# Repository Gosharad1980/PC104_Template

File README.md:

# PC104 template PCB

PC104 form factor compliant with the PC104_Spec_v2_6

## PC104 ISA 8bits

---
## PC104 ISA 16bits

---
## PC104 LibreCube

---
## PC104 "PCI CAN Express"
Custom connector designed from the PCI-Express(x1) pin-out

	Liaison :
	 - PRSNT1# et PRSNT2# par le GNDD (équivalent présence carte PCIx1)
	
	Remplacement :
	 - SMBus -> I2C
	 - JTAG -> SPI dont SC1# et SC2#
	 - WAKE# -> CS3#
	 - CLKREQ -> CLKO
	 - RefClk différentielle PCI -> OSC1 et OSC2 pour external clock MCU
	 - HSOp(0) soit TX0 PCI -> ModBus A+
	 - HSOn(0) soit TX0 PCI -> ModBus B-
	 - HSIp(0) soit RXO PCI -> CAN_0_H
	 - HSIn(0) soit RXO PCI -> CAN_0_L
	
	PS : 
	L'utilisation d'un RS485 4 fils est possibles en cablant :
	 - HSOp(0) soit TX0 PCI -> DI_A+ master / RO_A+ slave(s)
	 - HSOn(0) soit TX0 PCI -> DI_B- master / RO_B- slave(s)
	 - HSIp(0) soit RXO PCI -> RO_A+ master / DI_A+ slave(s)
	 - HSIn(0) soit RXO PCI -> RO_B- master / DI_B- slave(s)

	L'utilisation d'un RS485 2 fils est possibles en cablant :
	 - HSOp(0) soit TX0 PCI -> A+ master / A+ slave
	 - HSOn(0) soit TX0 PCI -> B- master / B- slave
	 - HSIp(0) soit RXO PCI -> NC. ou CAN_0_H
	 - HSIn(0) soit RXO PCI -> NC. ou CAN_0_L

---

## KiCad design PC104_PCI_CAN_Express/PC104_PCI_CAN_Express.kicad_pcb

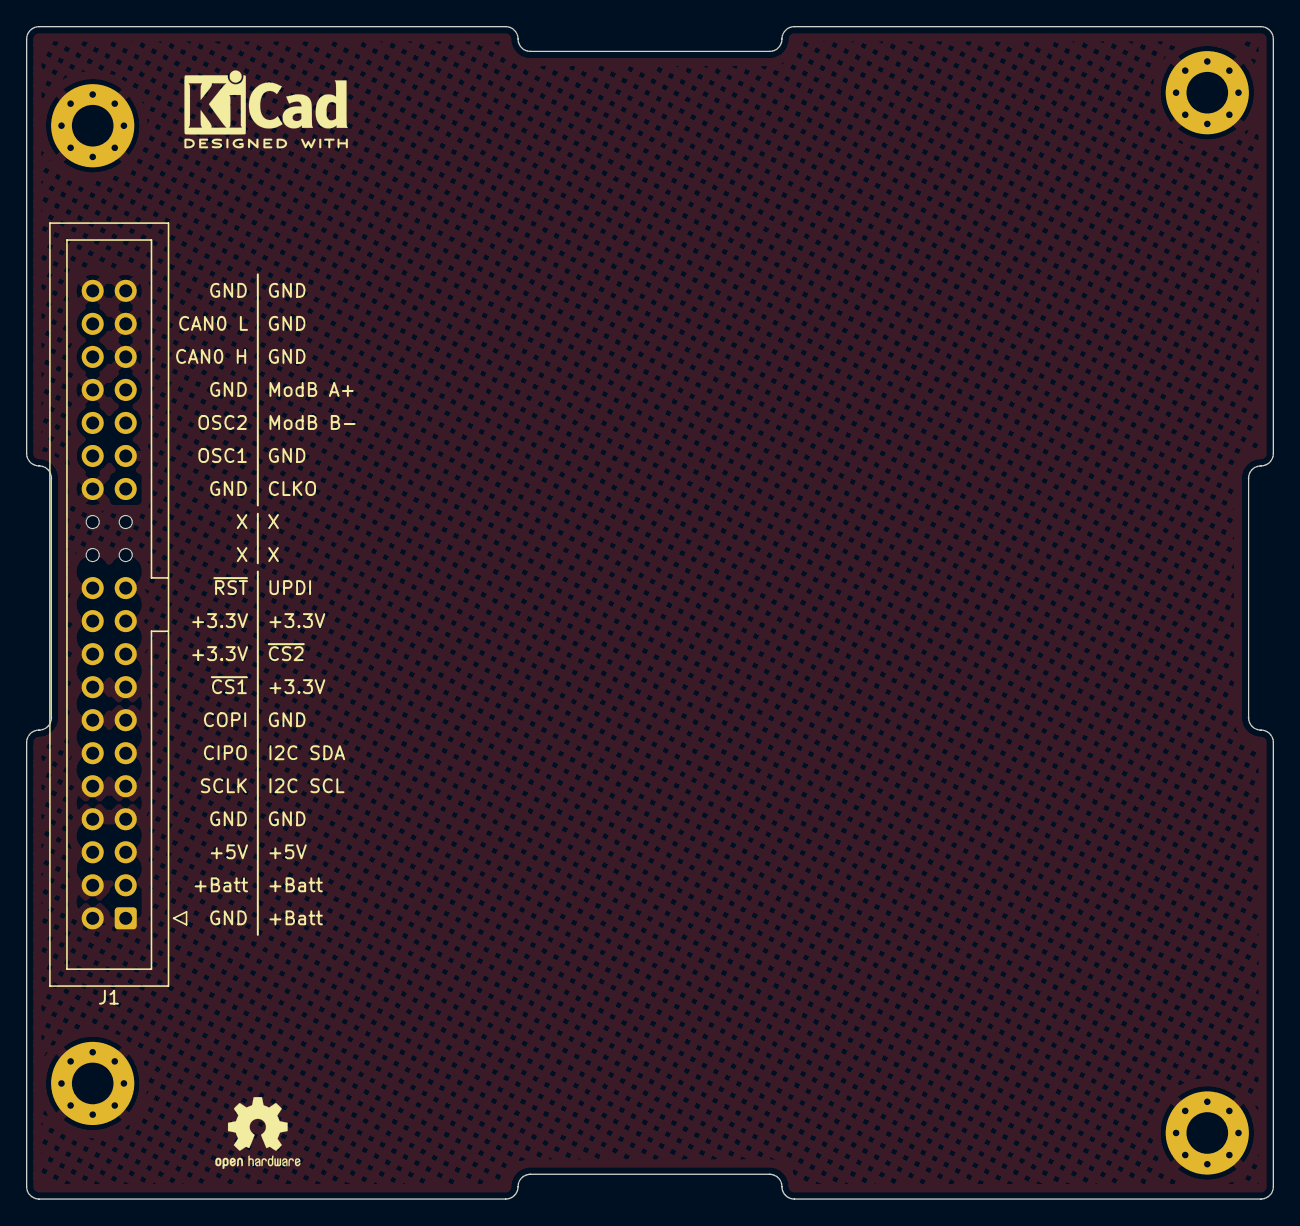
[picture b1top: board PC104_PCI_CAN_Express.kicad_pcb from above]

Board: 2 copper layers, 95.9 x 90.2 mm, 7 parts (0 on the bottom side), 4 nets, no tracks yet.

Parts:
H1, H2, H3, H4: MountingHole_Pad; MountingHole_3.2mm_M3_Pad_Via
J1: Conn_02x20_Odd_Even; IDC-Header_2x20_P2.54mm_Vertical
KiCad0: MountingHole; KiCad-Logo2_5mm_SilkScreen
OpenHW1: MountingHole; OSHW-Logo2_7.3x6mm_SilkScreen

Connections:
+3V3: J1.15, J1.18, J1.19, J1.20
+5V: J1.5, J1.6
+BATT: J1.1, J1.3, J1.4
GND: H1.1, H2.1, H3.1, H4.1, J1.2, J1.7, J1.8, J1.13, J1.28, J1.29, J1.34, J1.35, J1.37, J1.39, J1.40

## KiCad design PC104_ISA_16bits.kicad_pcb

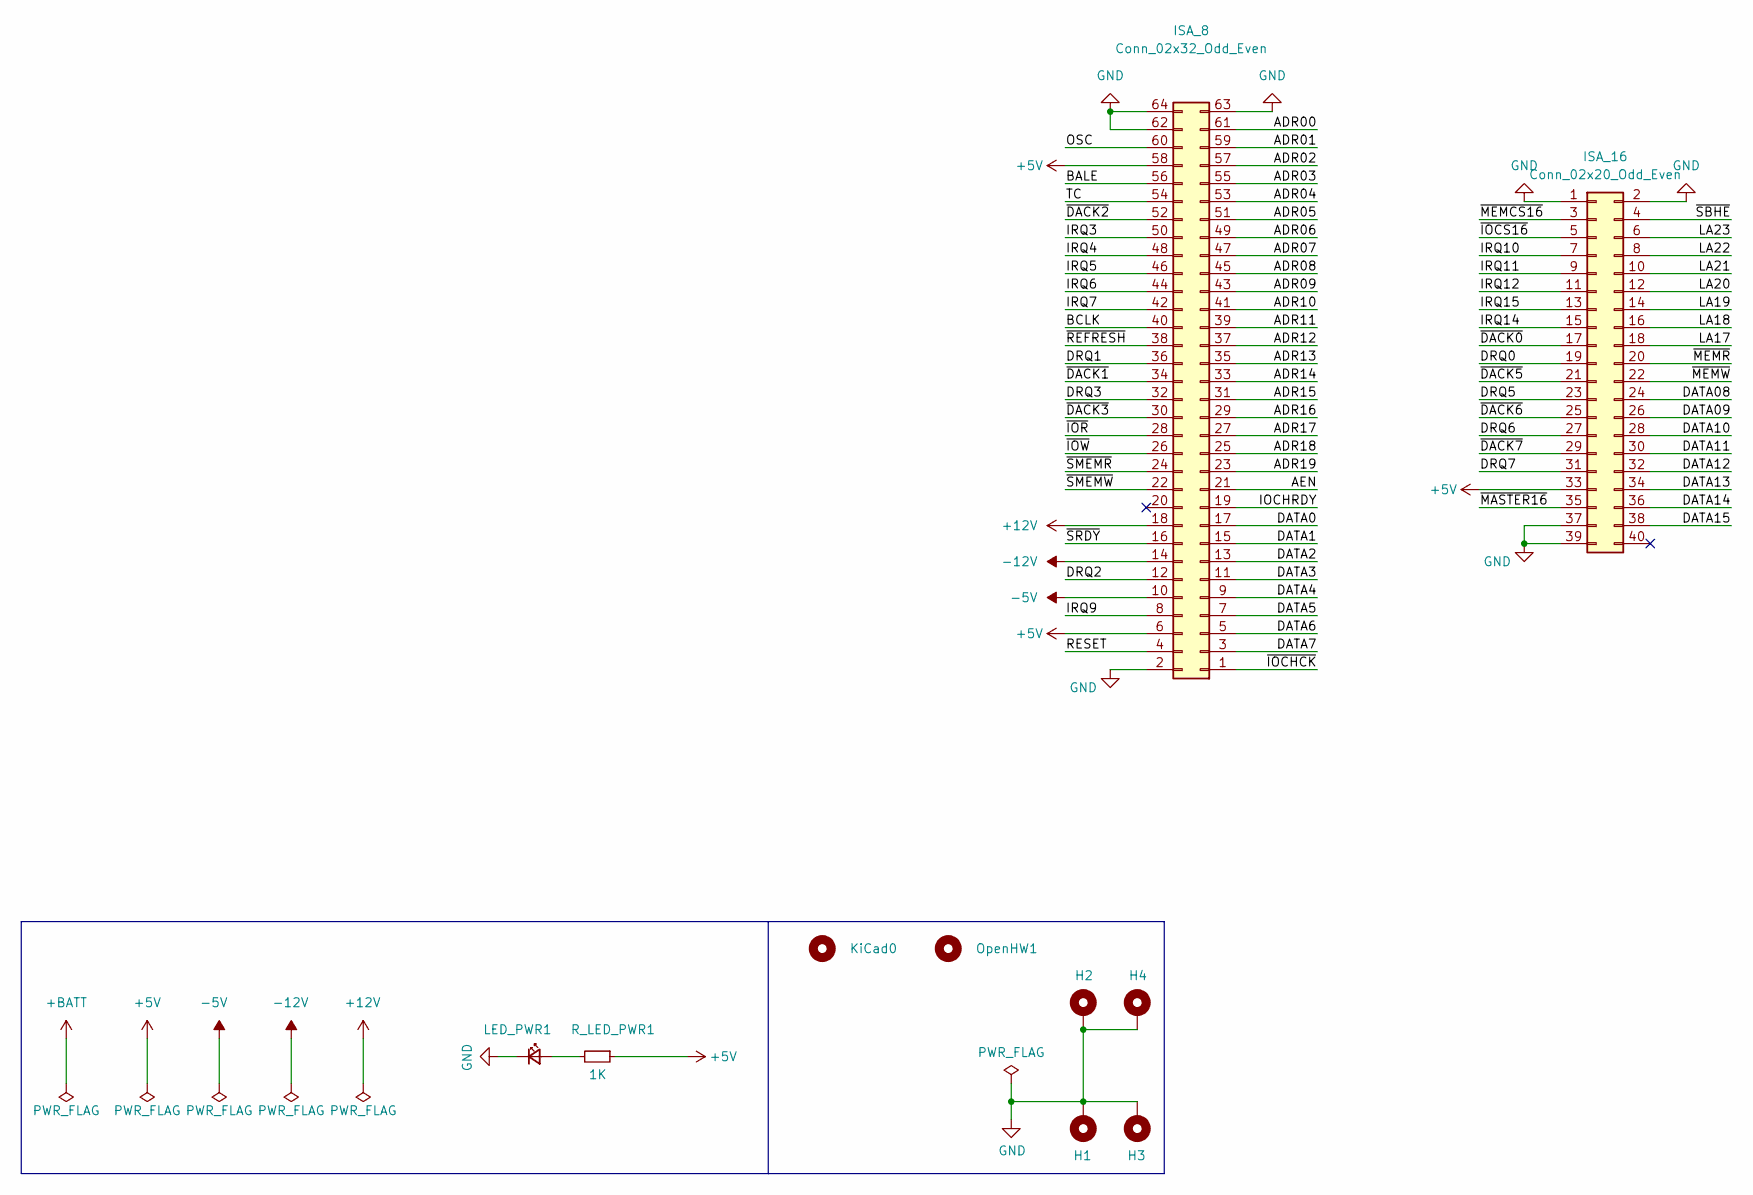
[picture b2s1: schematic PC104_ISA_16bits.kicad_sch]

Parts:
H1, H2, H3, H4: MountingHole_Pad; MountingHole_3.2mm_M3_DIN965_Pad
ISA_8: Conn_02x32_Odd_Even; PinHeader_2x32_P2.54mm_Vertical
ISA_16: Conn_02x20_Odd_Even; PinHeader_2x20_P2.54mm_Vertical
KiCad0: MountingHole; KiCad-Logo2_5mm_SilkScreen
LED_PWR1: LED; LED_1210_3225Metric_Pad1.42x2.65mm_HandSolder
OpenHW1: MountingHole; OSHW-Logo2_7.3x6mm_SilkScreen
R_LED_PWR1: 1K; R_1210_3225Metric_Pad1.30x2.65mm_HandSolder

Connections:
+5V: ISA_8.6, ISA_8.58, ISA_16.33, R_LED_PWR1.1
+12V: ISA_8.18
-5V: ISA_8.10
-12V: ISA_8.14
/ADR00: ISA_8.61
/ADR01: ISA_8.59
/ADR02: ISA_8.57
/ADR03: ISA_8.55
/ADR04: ISA_8.53
/ADR05: ISA_8.51
/ADR06: ISA_8.49
/ADR07: ISA_8.47
/ADR08: ISA_8.45
/ADR09: ISA_8.43
/ADR10: ISA_8.41
/ADR11: ISA_8.39
/ADR12: ISA_8.37
/ADR13: ISA_8.35
/ADR14: ISA_8.33
/ADR15: ISA_8.31
/ADR16: ISA_8.29
/ADR17: ISA_8.27
/ADR18: ISA_8.25
/ADR19: ISA_8.23
/AEN: ISA_8.21
/BALE: ISA_8.56
/BCLK: ISA_8.40
/DATA0: ISA_8.17
/DATA1: ISA_8.15
/DATA2: ISA_8.13
/DATA3: ISA_8.11
/DATA4: ISA_8.9
/DATA5: ISA_8.7
/DATA6: ISA_8.5
/DATA7: ISA_8.3
/DATA08: ISA_16.24
/DATA09: ISA_16.26
/DATA10: ISA_16.28
/DATA11: ISA_16.30
/DATA12: ISA_16.32
/DATA13: ISA_16.34
/DATA14: ISA_16.36
/DATA15: ISA_16.38
/DRQ0: ISA_16.19
/DRQ1: ISA_8.36
/DRQ2: ISA_8.12
/DRQ3: ISA_8.32
/DRQ5: ISA_16.23
/DRQ6: ISA_16.27
/DRQ7: ISA_16.31
/IOCHRDY: ISA_8.19
/IRQ3: ISA_8.50
/IRQ4: ISA_8.48
/IRQ5: ISA_8.46
/IRQ6: ISA_8.44
/IRQ7: ISA_8.42
/IRQ9: ISA_8.8
/IRQ10: ISA_16.7
/IRQ11: ISA_16.9
/IRQ12: ISA_16.11
/IRQ14: ISA_16.15
/IRQ15: ISA_16.13
/LA17: ISA_16.18
/LA18: ISA_16.16
/LA19: ISA_16.14
/LA20: ISA_16.12
/LA21: ISA_16.10
/LA22: ISA_16.8
/LA23: ISA_16.6
/OSC: ISA_8.60
/RESET: ISA_8.4
/TC: ISA_8.54
/~DACK0: ISA_16.17
/~DACK1: ISA_8.34
/~DACK2: ISA_8.52
/~DACK3: ISA_8.30
/~DACK5: ISA_16.21
/~DACK6: ISA_16.25
/~DACK7: ISA_16.29
/~IOCHCK: ISA_8.1
/~IOCS16: ISA_16.5
/~IOR: ISA_8.28
/~IOW: ISA_8.26
/~MASTER16: ISA_16.35
/~MEMCS16: ISA_16.3
/~MEMR: ISA_16.20
/~MEMW: ISA_16.22
/~REFRESH: ISA_8.38
/~SBHE: ISA_16.4
/~SMEMR: ISA_8.24
/~SMEMW: ISA_8.22
/~SRDY: ISA_8.16
GND: H1.1, H2.1, H3.1, H4.1, ISA_8.2, ISA_8.62, ISA_8.63, ISA_8.64, ISA_16.1, ISA_16.2, ISA_16.37, ISA_16.39, LED_PWR1.1 (K)
unnamed: LED_PWR1.2 (A), R_LED_PWR1.2

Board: 2 copper layers, 10 parts (0 on the bottom side), 3 nets, no tracks yet.

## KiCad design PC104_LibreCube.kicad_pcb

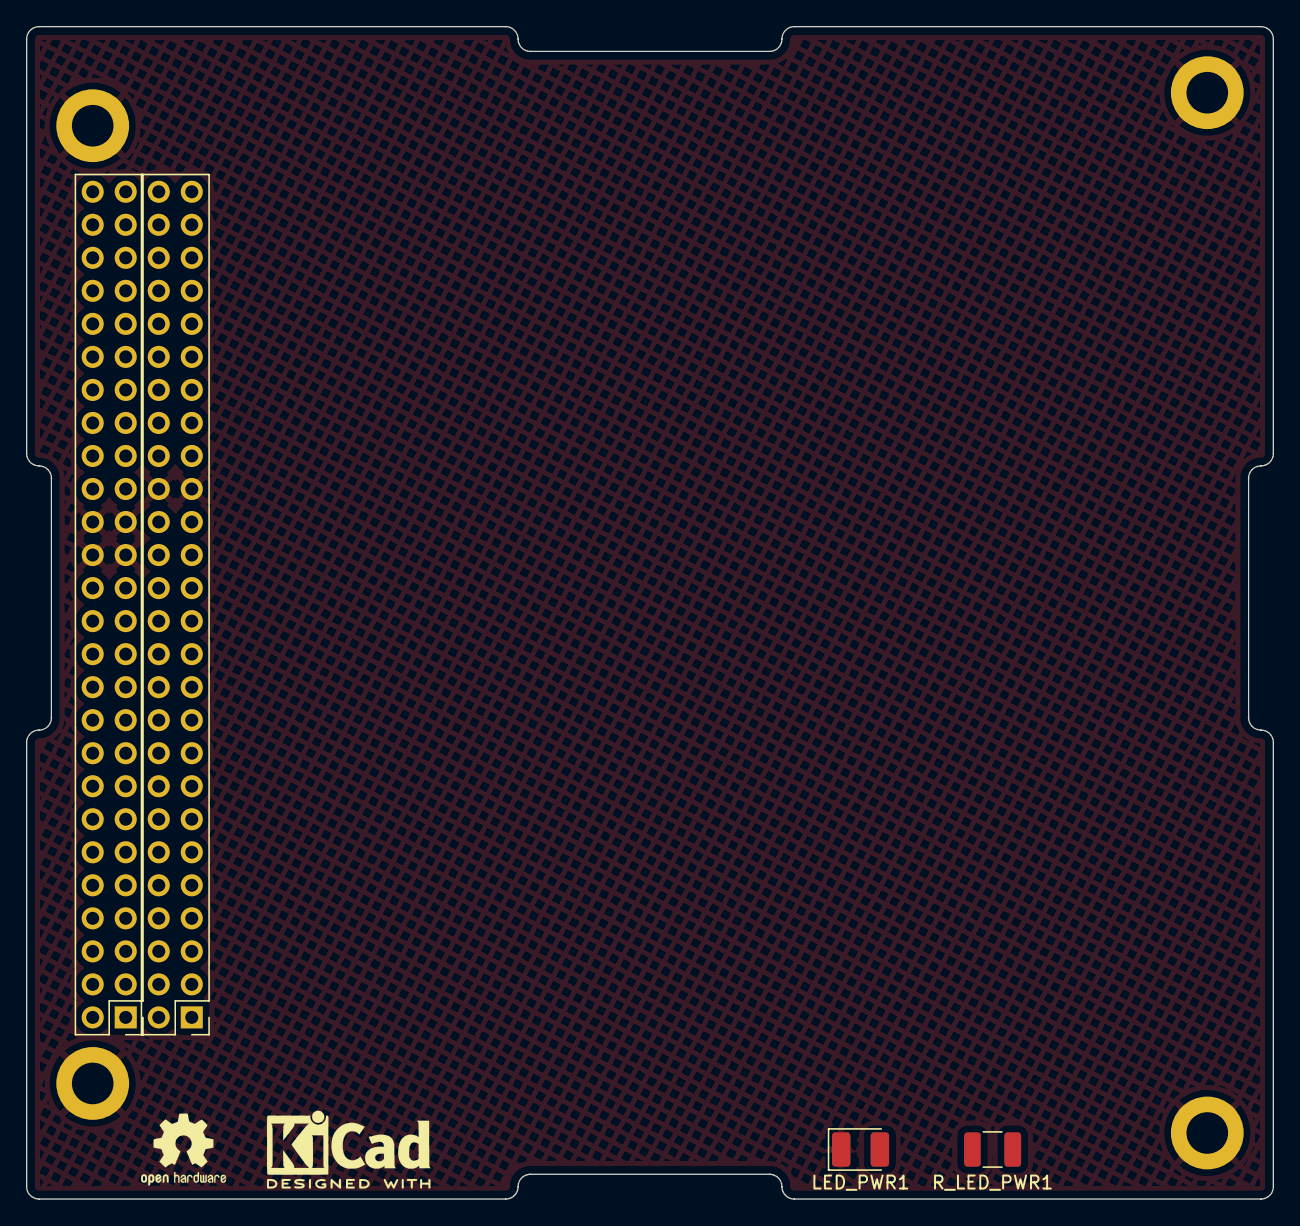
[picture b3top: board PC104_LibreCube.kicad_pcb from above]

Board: 2 copper layers, 95.9 x 90.2 mm, 10 parts (0 on the bottom side), 5 nets, no tracks yet.

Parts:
H1, H2, H3, H4: MountingHole_Pad; MountingHole_3.2mm_M3_DIN965_Pad
KiCad0: MountingHole; KiCad-Logo2_5mm_SilkScreen
LED_PWR1: LED; LED_1210_3225Metric_Pad1.42x2.65mm_HandSolder
LibreCube_H1, LibreCube_H2: Conn_02x26_Odd_Even; PinHeader_2x26_P2.54mm_Vertical
OpenHW1: MountingHole; OSHW-Logo2_7.3x6mm_SilkScreen
R_LED_PWR1: 1K; R_1210_3225Metric_Pad1.30x2.65mm_HandSolder

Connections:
+5V: LibreCube_H2.25, LibreCube_H2.26, R_LED_PWR1.1
+BATT: LibreCube_H2.45, LibreCube_H2.46
/CHARGE: LibreCube_H1.31, LibreCube_H1.32
GND: H1.1, H2.1, H3.1, H4.1, LED_PWR1.1 (K), LibreCube_H1.33, LibreCube_H1.34, LibreCube_H2.29, LibreCube_H2.30, LibreCube_H2.31, LibreCube_H2.32
unnamed: LED_PWR1.2 (A), R_LED_PWR1.2

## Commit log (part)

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2023-08-17 Imported folder structure
2023-08-17 Création de la branche PC104_ISA_8bits
2023-08-17 Création de la branche PC104_ISA_16bits
2023-08-17 Création de la branche PC104_LibreCube
2023-08-17 Création de la branche de ma connectique custom PC104_PCI_CAN_Express
2023-08-17 On init la branche
2023-08-18 Fin de l'init
2023-08-18 Init de la branche
2023-08-18 Suppression de la connectique LibreCube
2025-02-20 Fin conversion SVN -> GIT
2025-02-20 Ajout des specs PC104
2025-04-02 CORRECTION : connection +5V +3.3V +Batt au bus de fond de panier
2025-07-13 Adding : licence file for CC-BY-SA-4.0
    Update :
    - PC104_PCI_CAN_Express -> PCB silkscreen
2025-11-29 BUG : correction de la position du nouveau connecteur sur le PCB
